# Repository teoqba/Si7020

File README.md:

#Si7020 Arduino & Spark Core Library and Breakout board #

The software is released under GNU License.   
The PCB design is released under Creative Commons License.

## Library ##

Arduino and Spark Core library for Silicon Labs Si7020 relative humidity and temperature
sensor. When using Arduino, copy the files from firmware to Arduino IDE library folder. 
The sensor uses I2C communication. 

**USAGE:**  
See firmware/examples/Si7020\_example.ino for basic usage.

## Breakout ##
Bill of materials:
- 1 x Si7020 [Mouser] (http://www.mouser.com/ProductDetail/Silicon-Labs/Si7020-A10-GM1/?qs=sGAEpiMZZMsrQJTAfdCBRL5%2fWaPBRwpVjGUfQvjZXAsH9hImHflyUA%3d%3d)
- 2 x resistor 10kΩ [Digikey] (http://www.digikey.com/product-detail/en/ERJ-3GEYJ103V/P10KGCT-ND/134717)
- 1 x capacitor 0.1uF [Digikey] (http://www.digikey.com/product-detail/en/GRM188R71C104KA01D/490-1532-1-ND/587771)
- 1 x JST-SH 4pin [Digikey] (http://www.digikey.com/product-detail/en/SM04B-SRSS-TB(LF)(SN)/455-1804-1-ND/926875)

For the photo of assembled board see PCB/Si7020BB.jpg

## Connecting to Arduino ##
- VCC - Arduino 3.3V
- SDA - Arduino pin A4
- SCL - Arduino pin A5
- GND - Arduino GND

## Connecting to Spark Core ##
- VCC - Spark 3.3V
- SDA - Spark D0
- SCL - Spark D1
- GND - Spark GND

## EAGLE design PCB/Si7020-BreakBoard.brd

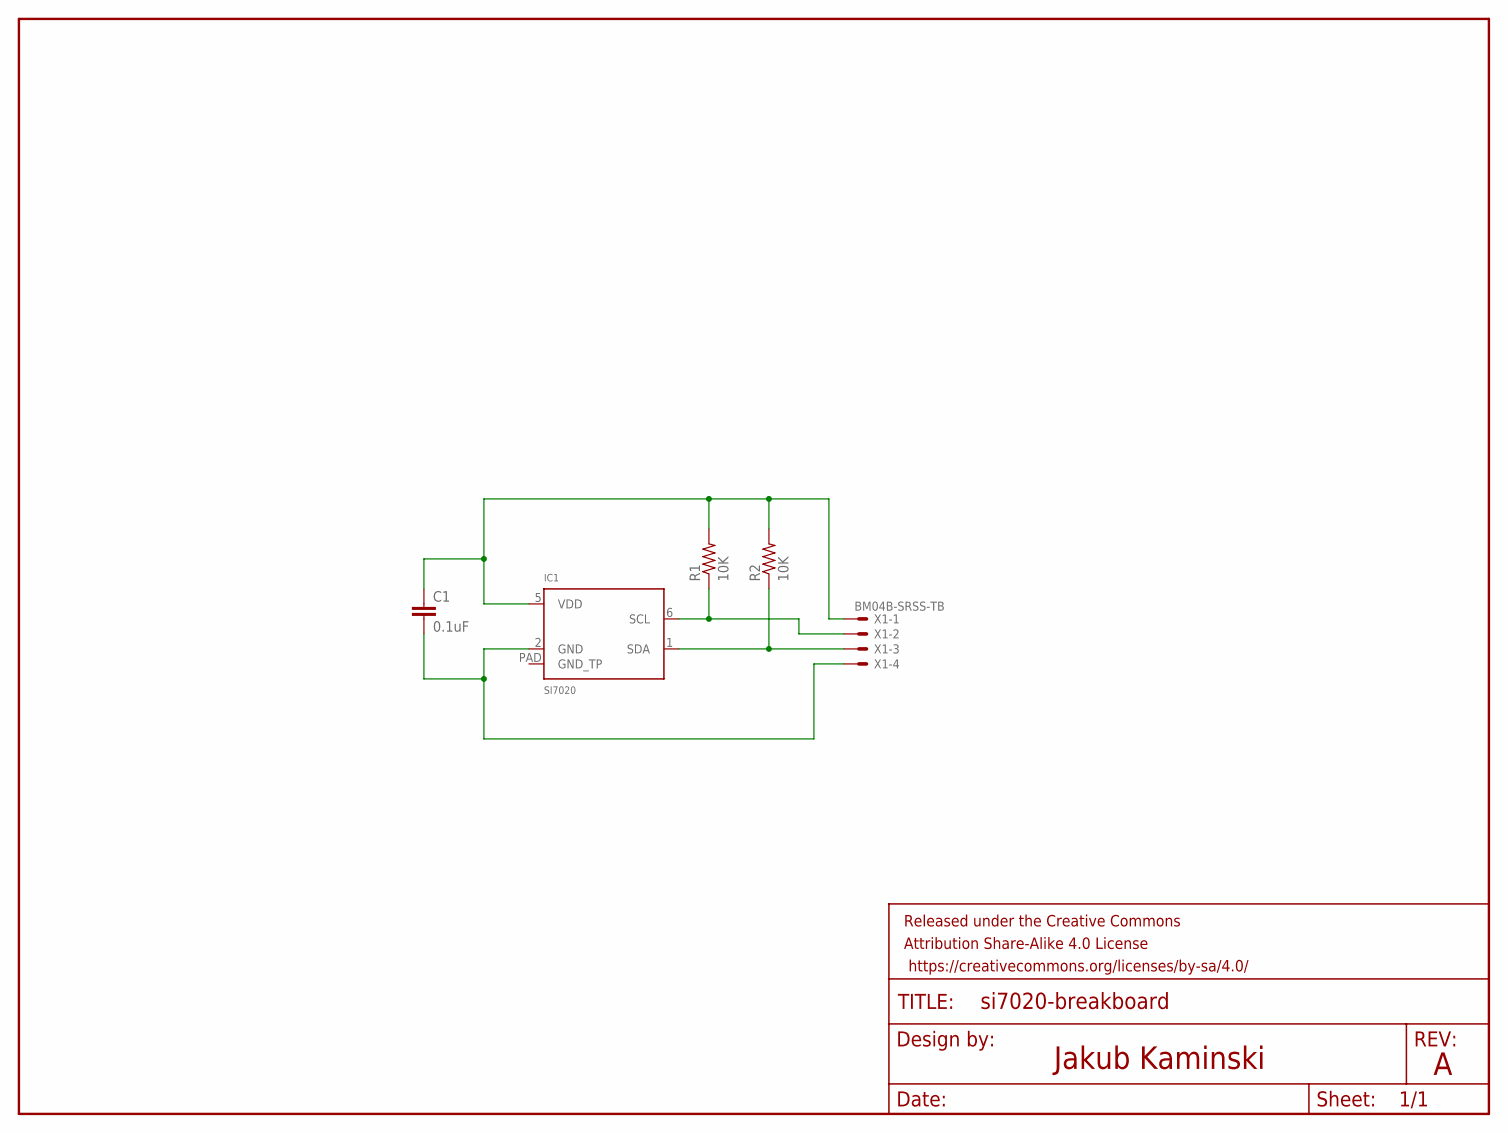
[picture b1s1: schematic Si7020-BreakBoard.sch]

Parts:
C1: 0.1uF; 0603-CAP
FRAME1: FRAME-LETTER; CREATIVE_COMMONS
IC1: SI7020; DFN6-3X3
R1, R2: 10K; 0603-RES
X1: BM04B-SRSS-TB

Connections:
unnamed: C1.1, IC1.5 (VDD), R1.2, R2.2, X1.1
unnamed: IC1.6 (SCL), R1.1, X1.2
unnamed: C1.2, IC1.2 (GND), X1.4
unnamed: IC1.1 (SDA), R2.1, X1.3

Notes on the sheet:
Jakub Kaminski

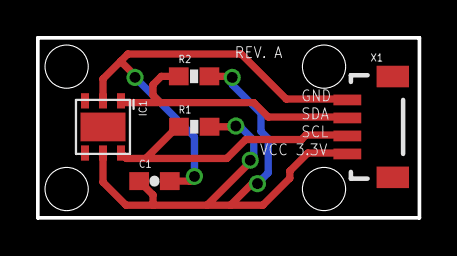
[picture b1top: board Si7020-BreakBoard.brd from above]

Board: 2 copper layers, 21.2 x 10.0 mm, 6 parts (0 on the bottom side), 4 nets.

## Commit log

2014-11-09 Rev.A, submitted to OSH park
2014-12-02 clean up
2014-12-02 Updated to library
2014-12-02 small README changes
2014-12-02 typos
2014-12-02 cleaning comments
2014-12-02 Fixed bug with units marks
2014-12-03 JSON added to the example
2014-12-07 Support for Spark Core added
2014-12-07 Added spark.json and LICENSE
2014-12-07 examples added
2014-12-07 updated dir structure
2014-12-08 Cleaning
2014-12-10 Default changed to NOHOLD, corrected typo
2014-12-10 Verion +0.0.1, Timeout return 100 for debugging
2014-12-10 More typos
2014-12-10 NO_HOLD delay changed to 100

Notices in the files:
parts and their libraries:
SparkFun-Capacitors: Licensing: Creative Commons ShareAlike 4.0 International - https://creativecommons.org/licenses/by-sa/4.0
SparkFun-Aesthetics: Released under the Creative Commons Attribution Share-Alike 4.0 License
SparkFun-Aesthetics: https://creativecommons.org/licenses/by-sa/4.0
